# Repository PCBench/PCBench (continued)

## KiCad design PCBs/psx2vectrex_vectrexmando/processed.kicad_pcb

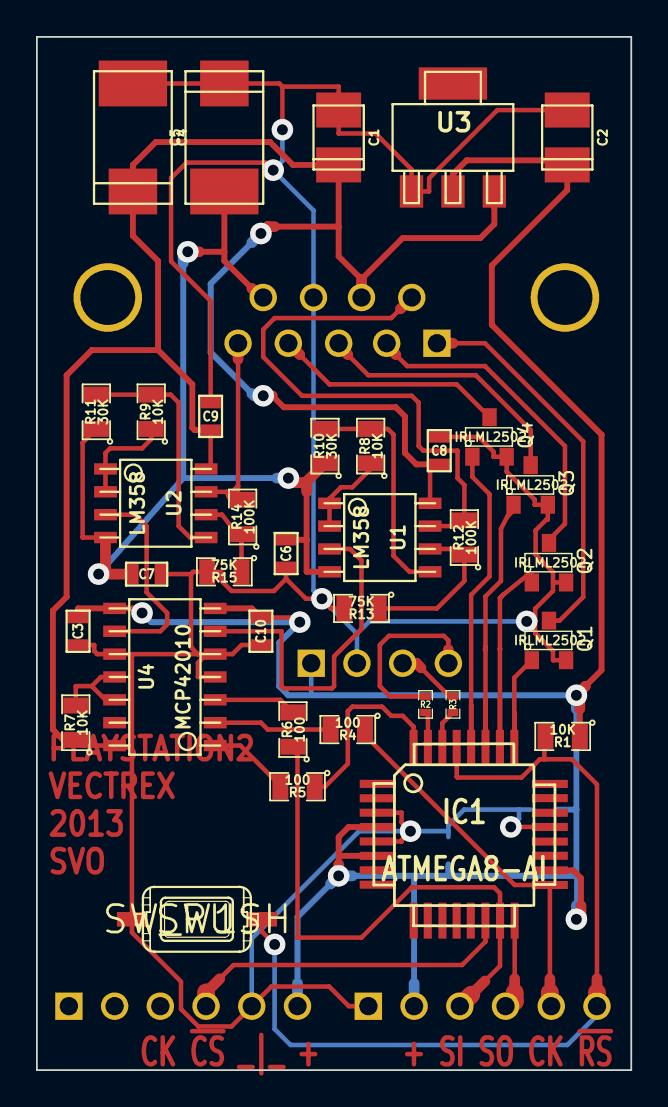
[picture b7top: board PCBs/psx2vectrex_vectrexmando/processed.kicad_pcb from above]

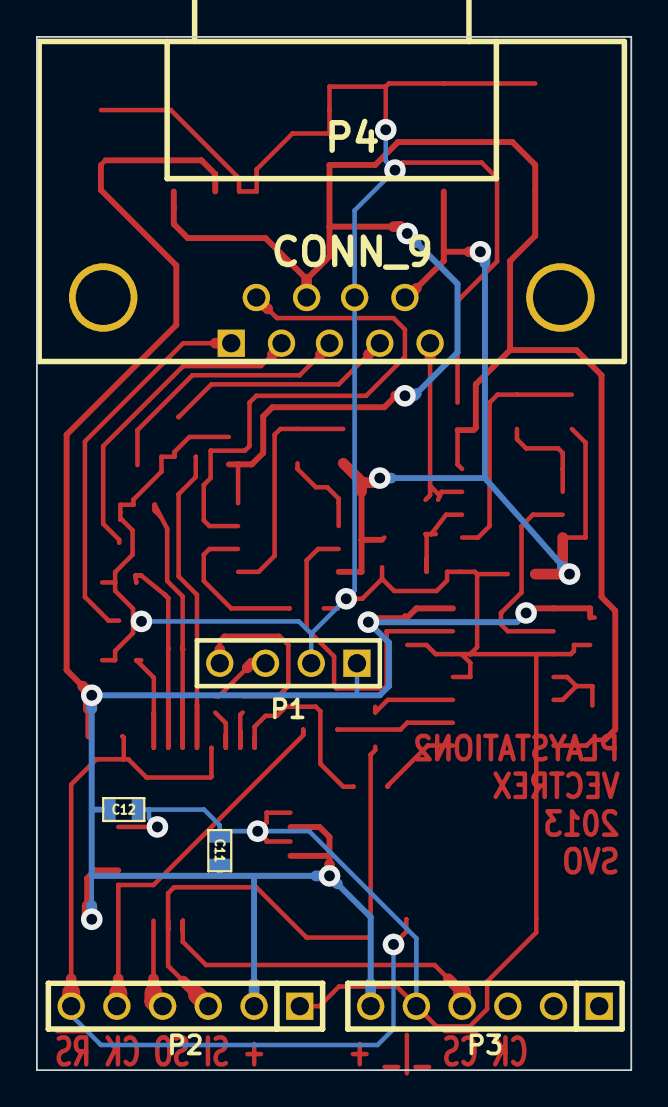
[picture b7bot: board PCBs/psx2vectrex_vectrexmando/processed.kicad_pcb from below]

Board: 2 copper layers, 33.0 x 57.4 mm, 41 parts (6 on the bottom side), 36 nets.

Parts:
C1, C2: 10; c_tant_B
C3, C6, C7, C8, C9, C10, C11, C12: 0.1; SM0603
C4, C5: 220; c_tant_D
IC1: ATMEGA8-AI; TQFP32
P1: CONN_4; PIN_ARRAY_4x1
P2, P3: CONN_6; PIN_ARRAY-6X1
P4: CONN_9; DB9FC
Q1, Q2, Q3, Q4: IRLML2502; SOT23
R1, R7, R8, R9: 10K; SM0805
R2, R3: 220; SM0402
R4, R5, R6: 100; SM0805
R10, R11: 30K; SM0805
R12, R14: 100K; SM0805
R13, R15: 75K; SM0805
SW1: SW_PUSH; 0-svo-SW_IT1181
U1, U2: LM358; so-8
U3: NCP1117ST33T3G; sot223
U4: MCP42010; so-14

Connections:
+3.3V: C2.1, C3.1, C10.1, C11.1, C12.1, IC1.4, IC1.6, IC1.18, P1.1, P2.2, P3.6, R1.1, U3.2, U4.7, U4.8
+5V: C1.1, C4.1, C8.1, C9.1, P4.7, R7.1, U1.8, U2.8, U3.3, U4.14
-5V: C5.2, C6.1, C7.1, P4.9, R10.1, R11.1, U1.4, U2.4
/LBUTT1: IC1.25, Q1.1
/LBUTT2: IC1.26, Q2.1
/LBUTT3: IC1.27, Q3.1
/LBUTT4: IC1.28, Q4.1
/MISO: IC1.16, P2.4
/MOSI: IC1.15, P2.3, R6.1
/POTX: U1.3, U4.6
/POTY: U2.3, U4.9
/RxD: IC1.30, R3.2
/SCK: IC1.17, P2.5, R4.1
/TxD: IC1.31, R2.2
/VBUTT1: P4.1, Q1.3
/VBUTT2: P4.2, Q2.3
/VBUTT3: P4.3, Q3.3
/VBUTT4: P4.4, Q4.3
/VX: P4.5, R14.2, U2.7
/VY: P4.6, R12.2, U1.7
/~POTCS: IC1.32, R5.1
/~PS2CS: IC1.14, P3.4
/~RESET: IC1.29, P2.6, R1.2, SW1.1
GND: C1.2, C2.2, C3.2, C4.2, C5.1, C6.2, C7.2, C8.2, C9.2, C10.2, C11.2, C12.2, IC1.3, IC1.5, IC1.21, P1.2, P2.1, P3.5, P4.8, Q1.2, Q2.2, Q3.2, Q4.2, R13.2, R15.2, SW1.2, U3.1, U4.4, U4.5, U4.10
unnamed: R7.2, U4.11, U4.12
unnamed: R5.2, U4.1
unnamed: R8.1, U1.1, U1.2
unnamed: R12.1, R13.1, U1.6
unnamed: R8.2, R10.2, U1.5
unnamed: P1.3, R3.1
unnamed: P1.4, R2.1
unnamed: R6.2, U4.3
unnamed: R9.1, U2.1, U2.2
unnamed: R9.2, R11.2, U2.5
unnamed: R14.1, R15.1, U2.6
unnamed: R4.2, U4.2
